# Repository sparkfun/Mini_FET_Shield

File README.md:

SparkFun Mini FET Shield
========================================

[*SparkFun Mini FET Shield (DEV-09627)*](https://www.sparkfun.com/products/9627)

 Developed by Dave Vondle and IDEO Labs, this board is essentially the same as our Power Driver Shield, but the through-hole parts have been switched out for smaller SMD construction, allowing you to to drive high-current switches with your Arduino Pro Mini. 
 This is a great shield for small prototyping.

 Repository Contents
-------------------

* **/Hardware** - Eagle design files (.brd, .sch)
* **/Production** - Production panel files (.brd)

Documentation
--------------
* **[Hookup Guide](https://learn.sparkfun.com/tutorials/mini-fet-shield-hookup-guide)** - Basic hookup guide for the Mini FET shield.
* **[SparkFun Fritzing repo](https://github.com/sparkfun/Fritzing_Parts)** - Fritzing diagrams for SparkFun products.
* **[SparkFun 3D Model repo](https://github.com/sparkfun/3D_Models)** - 3D models of SparkFun products. 

License Information
-------------------
This product is _**open source**_! 

The **hardware** is released under [Creative Commons ShareAlike 4.0 International](https://creativecommons.org/licenses/by-sa/4.0/).

Please use, reuse, and modify these files as you see fit. Please maintain attribution to SparkFun Electronics and release anything derivative under the same license.

Distributed as-is; no warranty is given.

- Your friends at SparkFun.

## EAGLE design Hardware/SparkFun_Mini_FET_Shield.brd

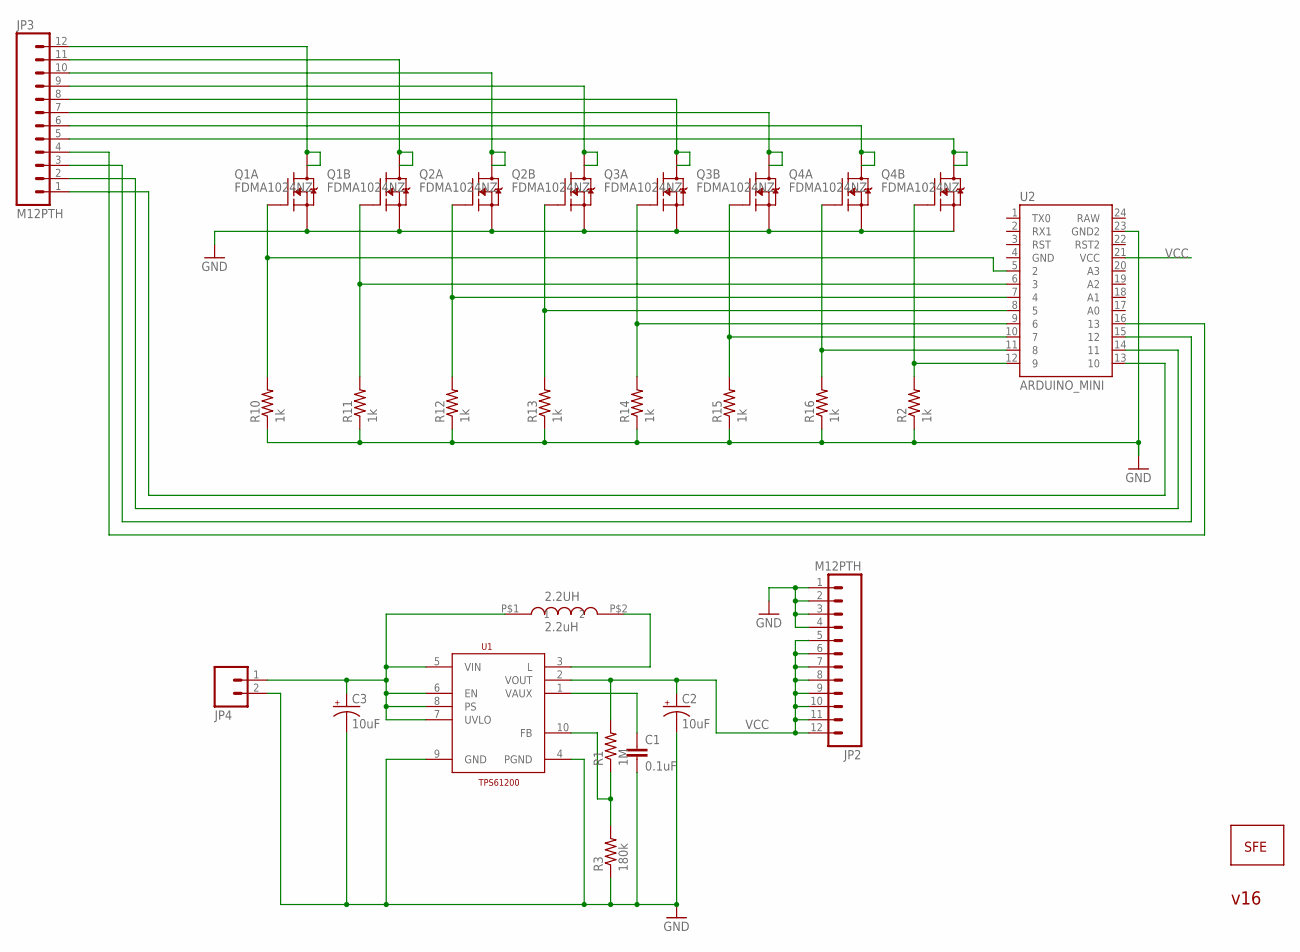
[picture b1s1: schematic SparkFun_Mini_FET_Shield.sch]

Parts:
2.2UH: 2.2uH; VLF4012A
C1: 0.1uF; 0402-CAP
C2, C3: 10uF; EIA3216
JP2, JP3: M12PTH; 1X12
JP4: M02PTH; 1X02
JP5: LOGO-SFESK; SFE-LOGO-FLAME
Q1, Q2, Q3, Q4: FDMA1024NZ; MICROFET_2X2
R1: 1M; 0402-RES
R2, R10, R11, R12, R13, R14, R15, R16: 1k; 0402-RES
R3: 180k; 0402-RES
U1: TPS61200; DRC-S-PVSON-N10
U2: ARDUINO_MINI

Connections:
GND: C1.2, C2.C (-), C3.C (-), JP2.1, JP2.2, JP2.3, JP2.4, JP4.2, Q1.S1 (S), Q1.S2 (S), Q2.S1 (S), Q2.S2 (S), Q3.S1 (S), Q3.S2 (S), Q4.S1 (S), Q4.S2 (S), R2.1, R3.1, R10.1, R11.1, R12.1, R13.1, R14.1, R15.1, R16.1, U1.4 (PGND), U1.9 (GND), U2.23 (GND2)
unnamed: JP3.4, U2.16 (13)
unnamed: R1.1, R3.2, U1.10 (FB)
unnamed: C1.1, U1.1 (VAUX)
unnamed: 2.2UH.P$2 (2), U1.3 (L)
unnamed: Q1.G1 (G), R10.2, U2.5 (2)
unnamed: 2.2UH.P$1 (1), C3.A (+), JP4.1, U1.5 (VIN), U1.6 (EN), U1.7 (UVLO), U1.8 (PS)
unnamed: Q1.G2 (G), R11.2, U2.6 (3)
unnamed: Q2.G1 (G), R12.2, U2.7 (4)
unnamed: Q2.G2 (G), R13.2, U2.8 (5)
unnamed: Q3.G1 (G), R14.2, U2.9 (6)
unnamed: Q3.G2 (G), R15.2, U2.10 (7)
unnamed: Q4.G1 (G), R16.2, U2.11 (8)
unnamed: Q4.G2 (G), R2.2, U2.12 (9)
unnamed: JP3.12, Q1.D1 (D), Q1.D1_2 (D1)
unnamed: JP3.11, Q1.D2 (D), Q1.D2_2 (D1)
unnamed: JP3.10, Q2.D1 (D), Q2.D1_2 (D1)
unnamed: JP3.9, Q2.D2 (D), Q2.D2_2 (D1)
unnamed: JP3.8, Q3.D1 (D), Q3.D1_2 (D1)
unnamed: JP3.7, Q3.D2 (D), Q3.D2_2 (D1)
unnamed: JP3.6, Q4.D1 (D), Q4.D1_2 (D1)
unnamed: JP3.5, Q4.D2 (D), Q4.D2_2 (D1)
unnamed: JP3.3, U2.15 (12)
unnamed: JP3.2, U2.14 (11)
unnamed: JP3.1, U2.13 (10)
VCC: C2.A (+), JP2.5, JP2.6, JP2.7, JP2.8, JP2.9, JP2.10, JP2.11, JP2.12, R1.2, U1.2 (VOUT), U2.21 (VCC)

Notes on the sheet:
v16

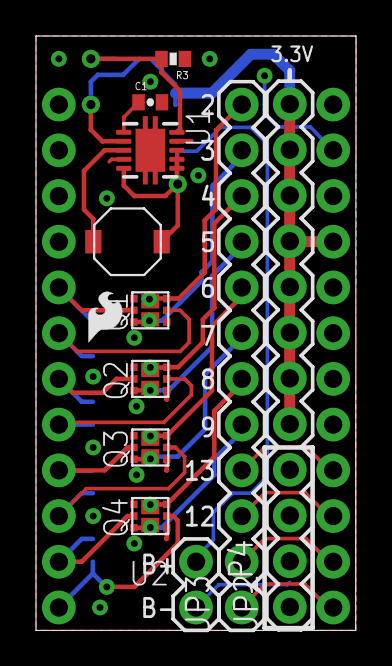
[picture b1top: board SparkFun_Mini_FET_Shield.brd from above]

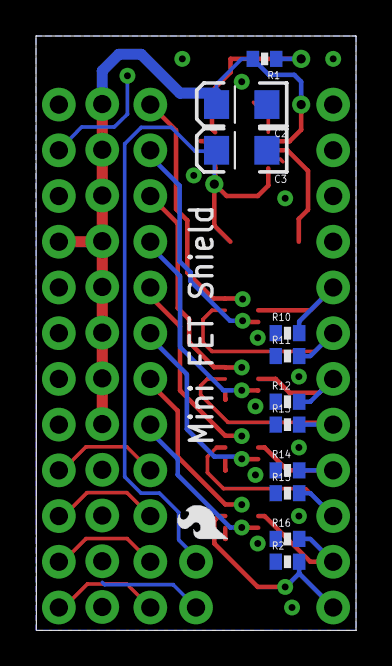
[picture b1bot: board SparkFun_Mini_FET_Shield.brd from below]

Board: 2 copper layers, 17.8 x 33.0 mm, 25 parts (12 on the bottom side), 26 nets.

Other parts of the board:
JP1: LOGO-SFESK; SFE-LOGO-FLAME

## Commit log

2015-05-07 Adding hardware files
